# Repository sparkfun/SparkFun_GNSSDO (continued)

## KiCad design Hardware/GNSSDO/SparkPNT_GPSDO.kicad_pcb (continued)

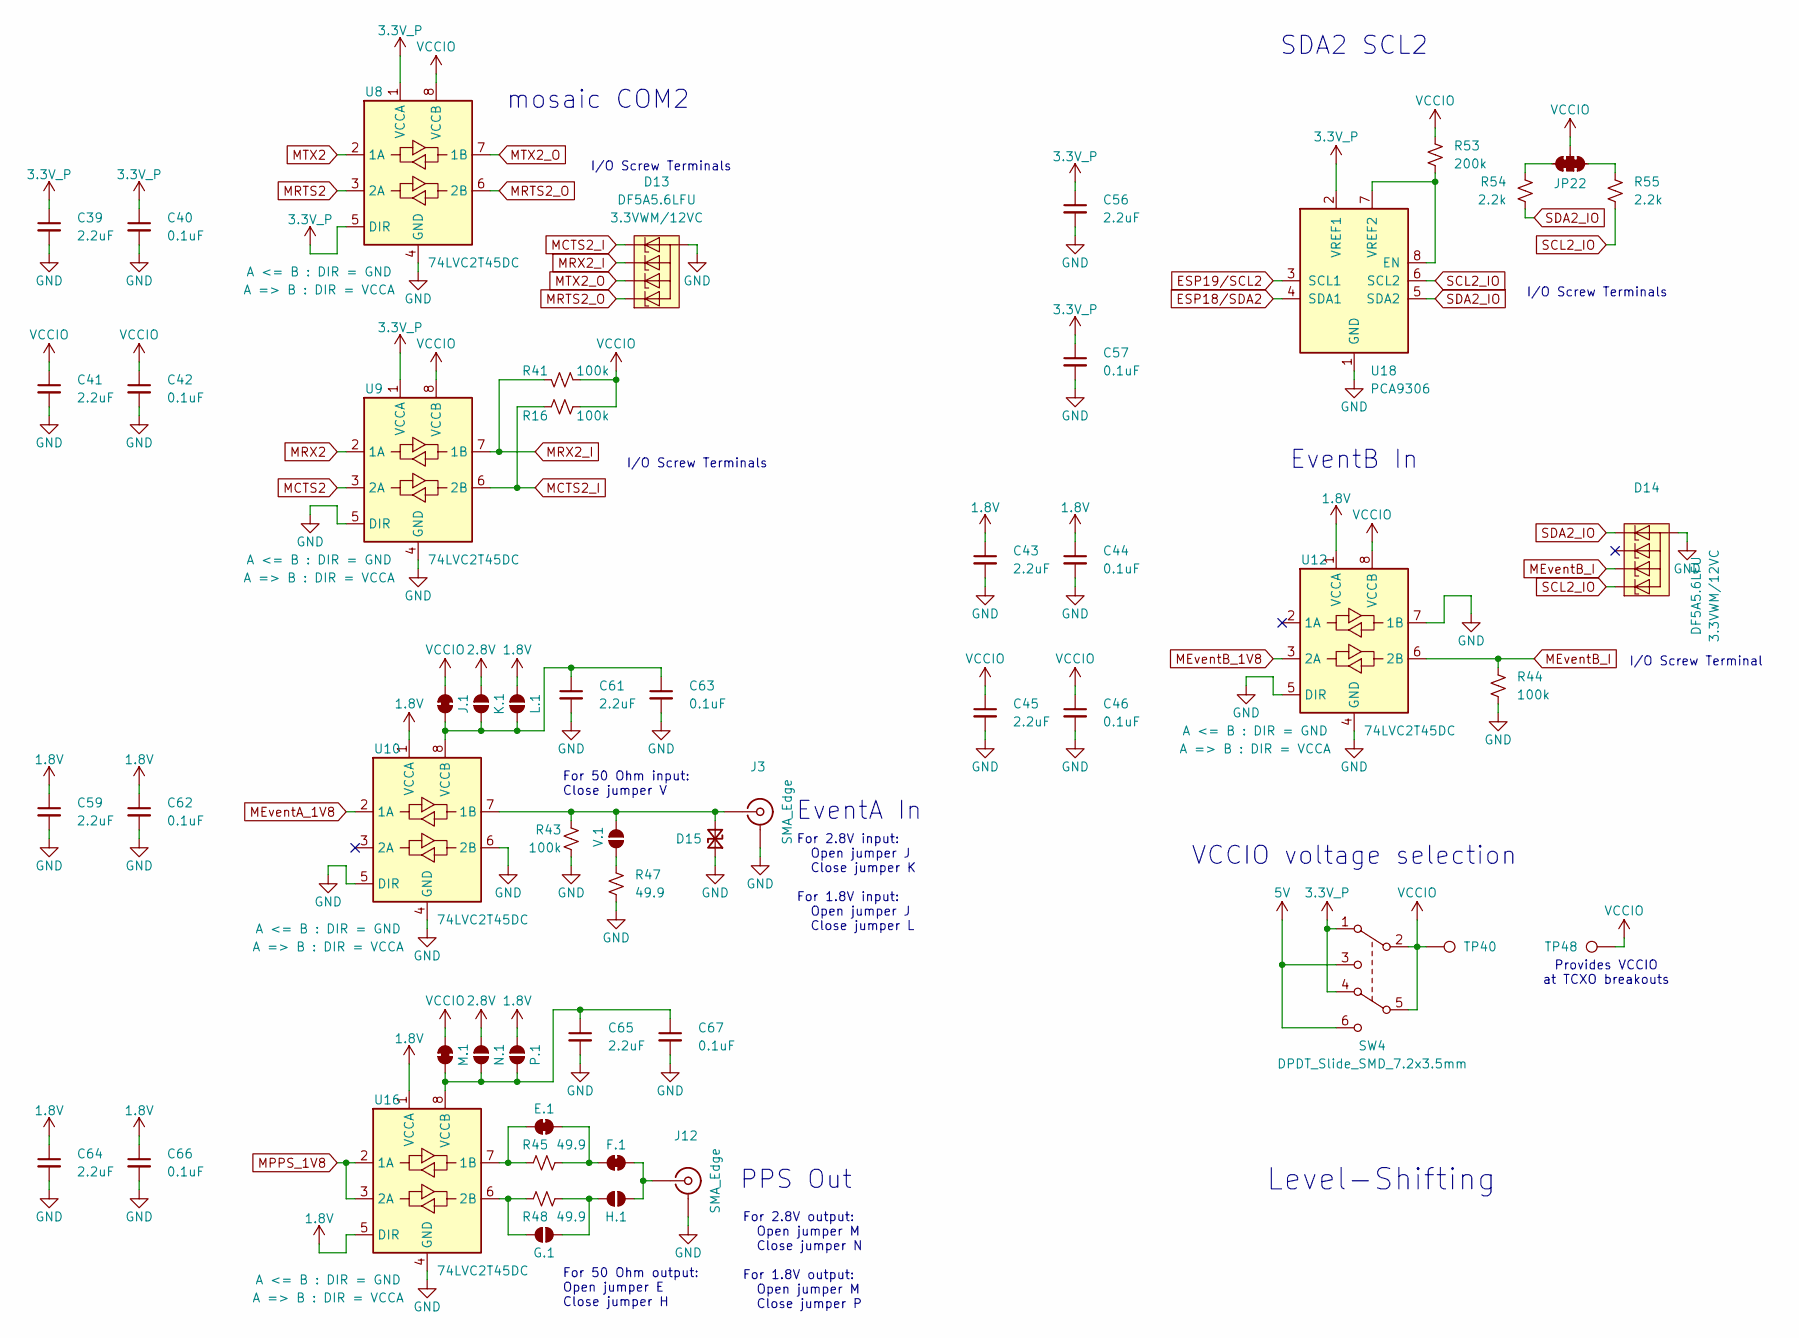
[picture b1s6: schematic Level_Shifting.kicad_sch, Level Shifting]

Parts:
C39, C41, C43, C45, C56, C59, C61, C64, C65: 2.2uF; C_0603_1608Metric; Voltage 10V; Tolerance 20%
C40, C42, C44, C46, C57, C62, C63, C66, C67: 0.1uF; C_0603_1608Metric; Voltage 25V; Tolerance 20%
D13, D14: DF5A5.6LFU; SOT-353; Rating 3.3VWM/12VC
D15: PESD0402; C_0402_1005Metric; Rating 14VWM/40VC
E.1: Jumper_2_NC_Trace
F.1: Jumper_2_NC_Trace
G.1: Jumper_2_NO
H.1: Jumper_2_NO
J3, J12: SMA_Edge; SMA_Edge_6.3mm
J.1: Jumper_2_NC_Trace
JP22: Jumper_3_NC-2_Trace
K.1: Jumper_2_NO
L.1: Jumper_2_NO
M.1: Jumper_2_NC_Trace
N.1: Jumper_2_NO
P.1: Jumper_2_NO
R16, R41, R43, R44: 100k; R_0603_1608Metric
R45, R47, R48: 49.9; R_0603_1608Metric; Tolerance 1%
R53: 200k; R_0603_1608Metric
R54, R55: 2.2k; R_0603_1608Metric
SW4: DPDT_Slide_SMD_7.2x3.5mm; Slide_DPDT_SMD_7.2x3.5mm; Mfg Part# ABC
TP40, TP48: PTH; 1x01_P2.54mm
U8, U9, U10, U12, U16: 74LVC2T45DC; VSSOP8_SOT765-1
U18: PCA9306; VSSOP8_SOT765-1
V.1: Jumper_2_NO

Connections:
1.8V: C43.1, C44.1, C59.1, C62.1, C64.1, C66.1, L.1.2 (B), P.1.2 (B), U10.1 (VCCA), U12.1 (VCCA), U16.1 (VCCA), U16.5 (DIR); also elsewhere on the board
2.8V: K.1.2 (B), N.1.2 (B); also elsewhere on the board
3.3V_P: C39.1, C40.1, C56.1, C57.1, SW4.1 (A), SW4.4 (A), U8.1 (VCCA), U8.5 (DIR), U9.1 (VCCA), U18.2 (VREF1); also elsewhere on the board
5V: SW4.3 (C), SW4.6 (C); also elsewhere on the board
ESP18/SDA2: U18.4 (SDA1); also elsewhere on the board
ESP19/SCL2: U18.3 (SCL1); also elsewhere on the board
GND: C39.2, C40.2, C41.2, C42.2, C43.2, C44.2, C45.2, C46.2, C56.2, C57.2, C59.2, C61.2, C62.2, C63.2, C64.2, C65.2, C66.2, C67.2, D13.2 (A), D14.2 (A), D15.1 (A1), J3.2 (Ext), J12.2 (Ext), R43.1, R44.1, R47.2, U8.4 (GND), U9.4 (GND), U9.5 (DIR), U10.4 (GND), U10.5 (DIR), U10.6 (2B), U12.4 (GND), U12.5 (DIR), U12.7 (1B), U16.4 (GND), U18.1 (GND); also elsewhere on the board
MCTS2: U9.3 (2A); also elsewhere on the board
MCTS2_I: D13.5 (K4), R16.1, U9.6 (2B); also elsewhere on the board
MEventA_1V8: U10.2 (1A); also elsewhere on the board
MEventB_1V8: U12.3 (2A); also elsewhere on the board
MEventB_I: D14.3 (K2), R44.2, U12.6 (2B); also elsewhere on the board
MPPS_1V8: U16.2 (1A), U16.3 (2A); also elsewhere on the board
MRTS2: U8.3 (2A); also elsewhere on the board
MRTS2_O: D13.1 (K1), U8.6 (2B); also elsewhere on the board
MRX2: U9.2 (1A); also elsewhere on the board
MRX2_I: D13.4 (K3), R41.1, U9.7 (1B); also elsewhere on the board
MTX2: U8.2 (1A); also elsewhere on the board
MTX2_O: D13.3 (K2), U8.7 (1B); also elsewhere on the board
unnamed: D15.2 (A2), J3.1 (In), R43.2, U10.7 (1B), V.1.2 (B)
unnamed: E.1.1 (A), R45.1, U16.7 (1B)
unnamed: E.1.2 (B), F.1.1 (A), R45.2
unnamed: F.1.2 (B), H.1.2 (B), J12.1 (In)
unnamed: G.1.1 (A), R48.1, U16.6 (2B)
unnamed: G.1.2 (B), H.1.1 (A), R48.2
unnamed: C61.1, C63.1, J.1.1 (A), K.1.1 (A), L.1.1 (A), U10.8 (VCCB)
unnamed: JP22.1 (A), R55.1
unnamed: JP22.3 (C), R54.1
unnamed: C65.1, C67.1, M.1.1 (A), N.1.1 (A), P.1.1 (A), U16.8 (VCCB)
unnamed: R53.2, U18.7 (VREF2), U18.8 (EN)
unnamed: R47.1, V.1.1 (A)
SCL2_IO: D14.1 (K1), R55.2, U18.6 (SCL2); also elsewhere on the board
SDA2_IO: D14.5 (K4), R54.2, U18.5 (SDA2); also elsewhere on the board
VCCIO: C41.1, C42.1, C45.1, C46.1, J.1.2 (B), JP22.2 (B), M.1.2 (B), R16.2, R41.2, R53.1, SW4.2 (B), SW4.5 (B), TP40.1 (1_1), TP48.1 (1_1), U8.8 (VCCB), U9.8 (VCCB), U12.8 (VCCB); also elsewhere on the board

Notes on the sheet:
SDA2 SCL2
I/O Screw Terminals
Provides VCCIO at TCXO breakouts
For 50 Ohm input: Close jumper V
mosaic COM2
I/O Screw Terminal
Level-Shifting
For 50 Ohm output: Open jumper E Close jumper H
For 2.8V input: Open jumper J Close jumper K For 1.8V input: Open jumper J Close jumper L
For 2.8V output: Open jumper M Close jumper N For 1.8V output: Open jumper M Close jumper P
EventB In
EventA In
PPS Out
VCCIO voltage selection

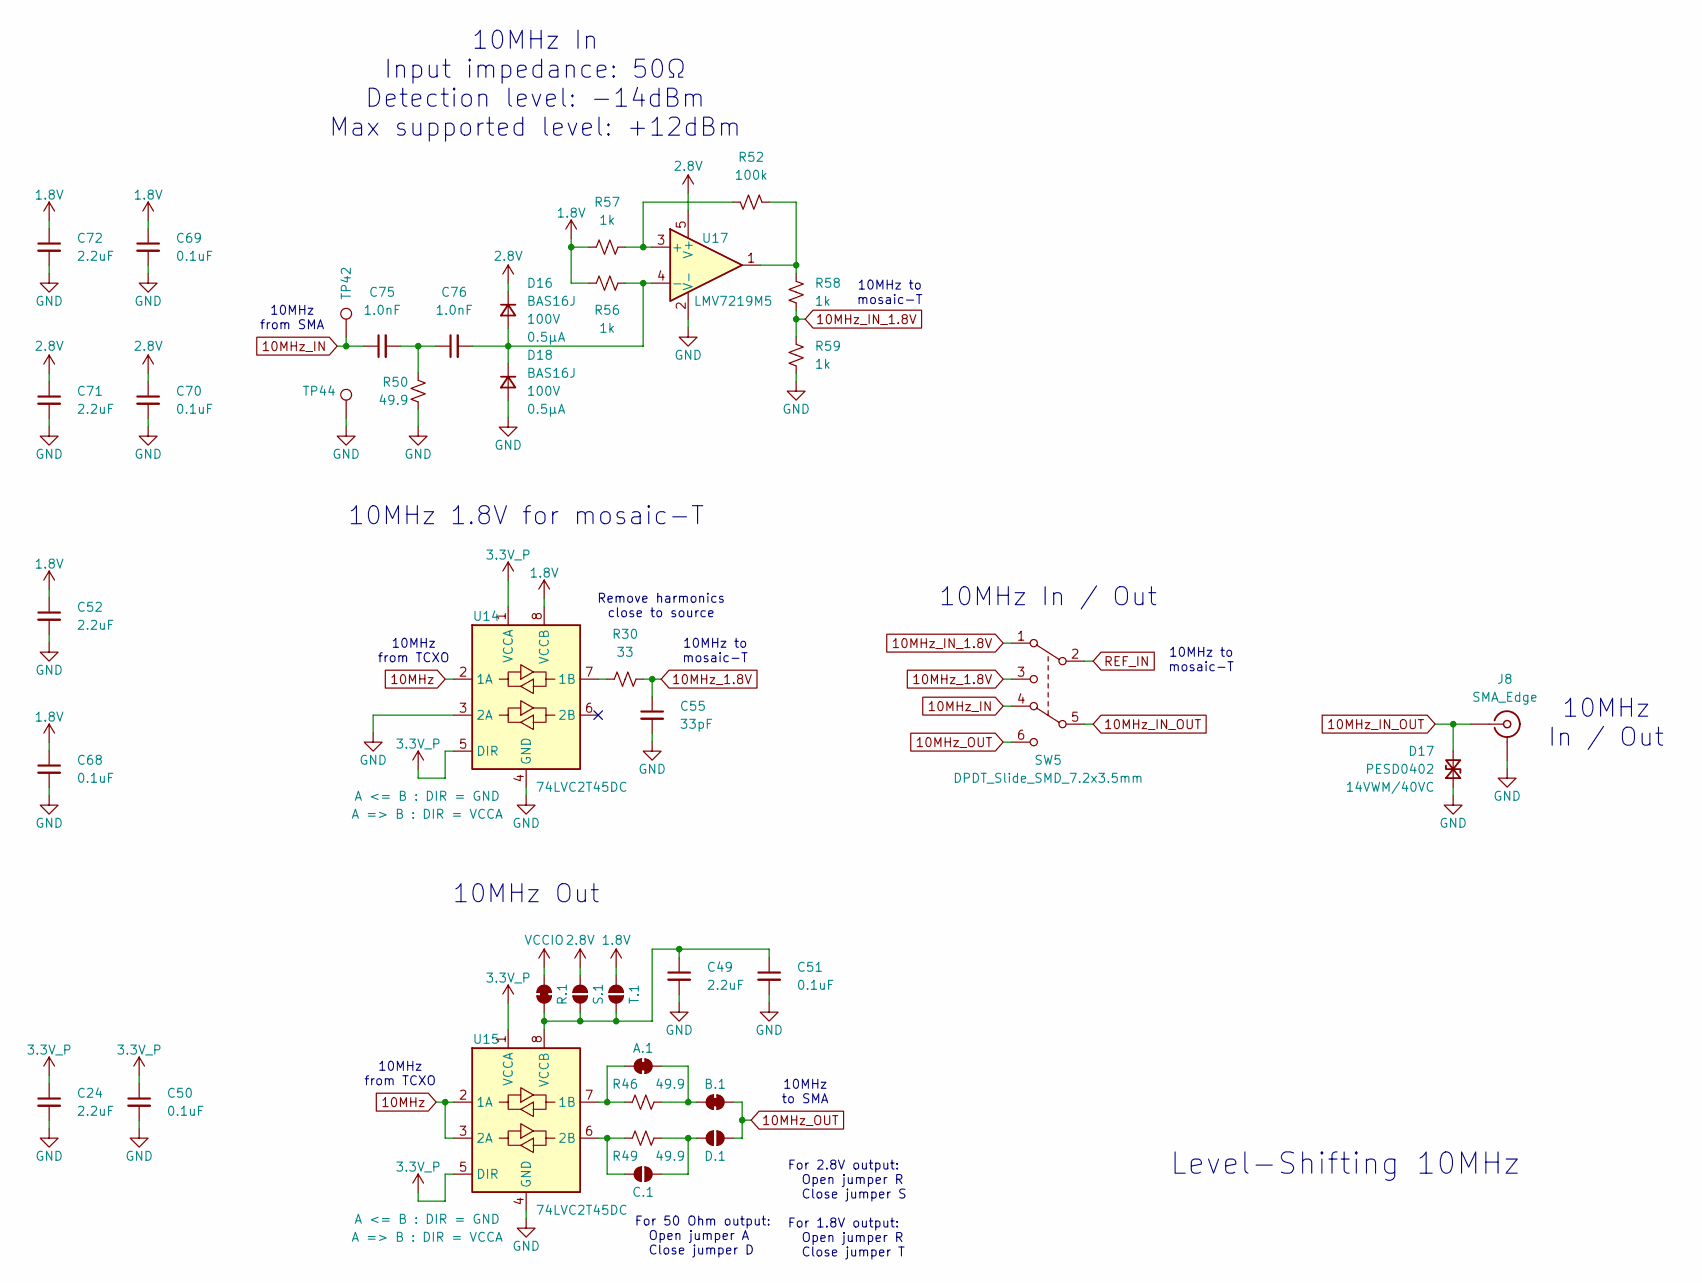
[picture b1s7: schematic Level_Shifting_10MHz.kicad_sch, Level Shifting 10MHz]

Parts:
A.1: Jumper_2_NC_Trace
B.1: Jumper_2_NC_Trace
C24, C49, C52, C71, C72: 2.2uF; C_0603_1608Metric; Voltage 10V; Tolerance 20%
C50, C51, C68, C69, C70: 0.1uF; C_0603_1608Metric; Voltage 25V; Tolerance 20%
C55: 33pF; C_0603_1608Metric; Voltage 50V; Tolerance 5%
C75, C76: 1.0nF; C_0603_1608Metric; Voltage 50V; Tolerance 10%
C.1: Jumper_2_NO
D16, D18: BAS16J; SOD-323
D17: PESD0402; C_0402_1005Metric; Rating 14VWM/40VC
D.1: Jumper_2_NO
J8: SMA_Edge; SMA_Edge_6.3mm
R30: 33; R_0603_1608Metric
R46, R49, R50: 49.9; R_0603_1608Metric; Tolerance 1%
R52: 100k; R_0603_1608Metric
R56, R57, R58, R59: 1k; R_0603_1608Metric
R.1: Jumper_2_NC_Trace
S.1: Jumper_2_NO
SW5: DPDT_Slide_SMD_7.2x3.5mm; Slide_DPDT_SMD_7.2x3.5mm; Mfg Part# ABC
T.1: Jumper_2_NO
TP42, TP44: PTH; 1x01_P2.54mm
U14, U15: 74LVC2T45DC; VSSOP8_SOT765-1
U17: LMV7219M5; SOT23-5

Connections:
1.8V: C52.1, C68.1, C69.1, C72.1, R56.2, R57.2, T.1.2 (B), U14.8 (VCCB); also elsewhere on the board
2.8V: C70.1, C71.1, D16.1 (K), S.1.2 (B), U17.5 (V+); also elsewhere on the board
3.3V_P: C24.1, C50.1, U14.1 (VCCA), U14.5 (DIR), U15.1 (VCCA), U15.5 (DIR); also elsewhere on the board
10MHz: U14.2 (1A), U15.2 (1A), U15.3 (2A); also elsewhere on the board
10MHz_1.8V: C55.1, R30.2, SW5.3 (C)
10MHz_IN: C75.1, SW5.4 (A), TP42.1 (1_1)
10MHz_IN_1.8V: R58.2, R59.1, SW5.1 (A)
10MHz_IN_OUT: D17.2 (A2), J8.1 (In), SW5.5 (B)
10MHz_OUT: B.1.2 (B), D.1.2 (B), SW5.6 (C)
GND: C24.2, C49.2, C50.2, C51.2, C52.2, C55.2, C68.2, C69.2, C70.2, C71.2, C72.2, D17.1 (A1), D18.2 (A), J8.2 (Ext), R50.2, R59.2, TP44.1 (1_1), U14.3 (2A), U14.4 (GND), U15.4 (GND), U17.2 (V-); also elsewhere on the board
unnamed: A.1.1 (A), R46.1, U15.7 (1B)
unnamed: A.1.2 (B), B.1.1 (A), R46.2
unnamed: C75.2, C76.1, R50.1
unnamed: C.1.1 (A), R49.1, U15.6 (2B)
unnamed: C.1.2 (B), D.1.1 (A), R49.2
unnamed: C76.2, D16.2 (A), D18.1 (K), R56.1, U17.4 (-)
unnamed: R52.2, R58.1, U17.1
unnamed: C49.1, C51.1, R.1.1 (A), S.1.1 (A), T.1.1 (A), U15.8 (VCCB)
unnamed: R30.1, U14.7 (1B)
unnamed: R52.1, R57.1, U17.3 (+)
REF_IN: SW5.2 (B); also elsewhere on the board
VCCIO: R.1.2 (B); also elsewhere on the board

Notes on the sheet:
10MHz from TCXO
10MHz from SMA
10MHz to mosaic-T
10MHz In Input impedance: 50Ω Detection level: -14dBm Max supported level: +12dBm
For 50 Ohm output: Open jumper A Close jumper D
10MHz In / Out
Remove harmonics close to source
For 2.8V output: Open jumper R Close jumper S For 1.8V output: Open jumper R Close jumper T
10MHz 1.8V for mosaic-T
Level-Shifting 10MHz
10MHz to SMA
10MHz In / Out
10MHz Out

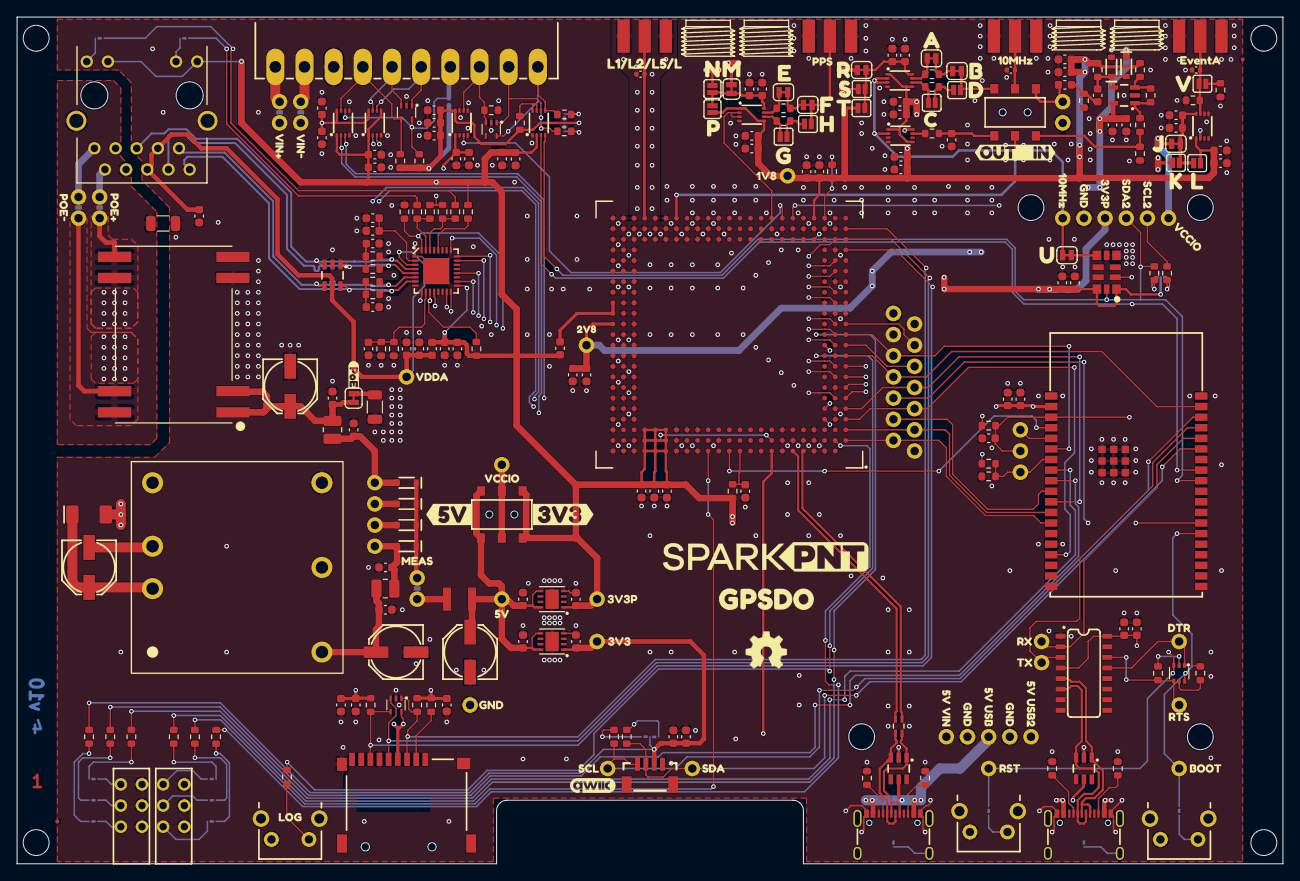
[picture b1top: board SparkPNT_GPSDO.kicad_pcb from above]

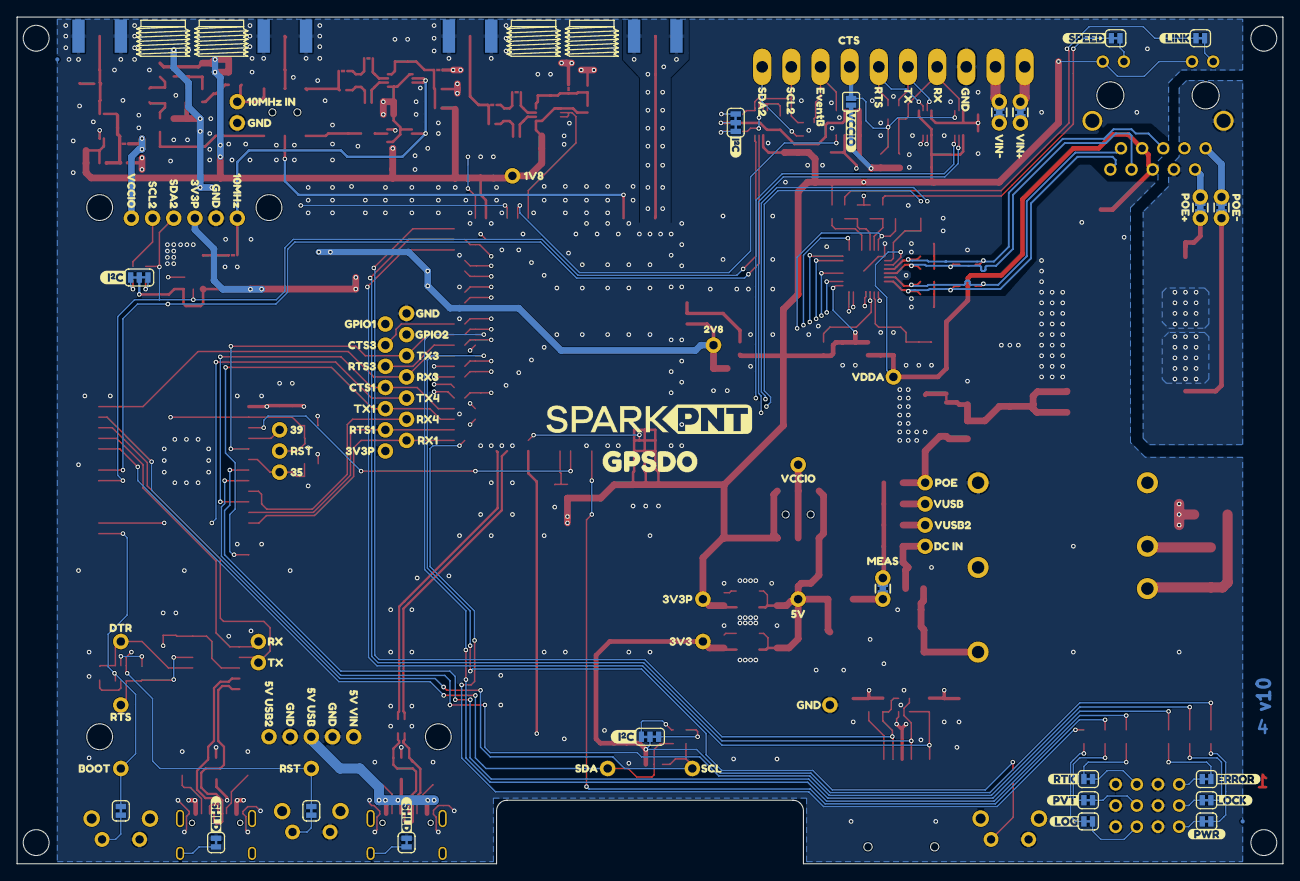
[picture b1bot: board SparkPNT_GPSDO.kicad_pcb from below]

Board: 4 copper layers, 151.9 x 101.6 mm, 435 parts (101 on the bottom side), 169 nets.

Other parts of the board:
Ref**: Val**; OSHW_Logo_5mm
kibuzzard-65A7F5A7: G***; kibuzzard-65A7F5A7
kibuzzard-65A7F5BC: G***; kibuzzard-65A7F5BC
kibuzzard-65A7F5CF: G***; kibuzzard-65A7F5CF
kibuzzard-65A7F5E3: G***; kibuzzard-65A7F5E3
kibuzzard-65A7F440, kibuzzard-65A7F440#2: G***; kibuzzard-65A7F440
kibuzzard-65A7F499: G***; kibuzzard-65A7F499
kibuzzard-65A7F511, kibuzzard-65A7F511#2: G***; kibuzzard-65A7F511
kibuzzard-65A7F548, kibuzzard-65A7F548#2: G***; kibuzzard-65A7F548
kibuzzard-65A7F771, kibuzzard-65A7F771#2: G***; kibuzzard-65A7F771
kibuzzard-65A7F891, kibuzzard-65A7F891#2: G***; kibuzzard-65A7F891
kibuzzard-66A11DB0: G***; kibuzzard-66A11DB0
kibuzzard-66A11DCF: G***; kibuzzard-66A11DCF
kibuzzard-66A11DE1: G***; kibuzzard-66A11DE1
kibuzzard-66A11DF6: G***; kibuzzard-66A11DF6
kibuzzard-66A11E3D: G***; kibuzzard-66A11E3D
kibuzzard-66A11E07: G***; kibuzzard-66A11E07
kibuzzard-66A11E7B: G***; kibuzzard-66A11E7B
kibuzzard-66A11E14: G***; kibuzzard-66A11E14
kibuzzard-66A11E22: G***; kibuzzard-66A11E22
kibuzzard-66A11E31: G***; kibuzzard-66A11E31
kibuzzard-66A11E48: G***; kibuzzard-66A11E48
kibuzzard-66A11E61: G***; kibuzzard-66A11E61
kibuzzard-66A11EB6, kibuzzard-66A11EB6#2: G***; kibuzzard-66A11EB6
kibuzzard-66A11ECA, kibuzzard-66A11ECA#2: G***; kibuzzard-66A11ECA
kibuzzard-66A11ED7, kibuzzard-66A11ED7#2, kibuzzard-66A11ED7#3: G***; kibuzzard-66A11ED7
kibuzzard-66A11EE6, kibuzzard-66A11EE6#2: G***; kibuzzard-66A11EE6
kibuzzard-66A11EF1, kibuzzard-66A11EF1#2: G***; kibuzzard-66A11EF1
kibuzzard-66A11F9C: G***; kibuzzard-66A11F9C
kibuzzard-66A11F21, kibuzzard-66A11F21#2: G***; kibuzzard-66A11F21
kibuzzard-66A11F39, kibuzzard-66A11F39#2: G***; kibuzzard-66A11F39
kibuzzard-66A11FB3: G***; kibuzzard-66A11FB3
kibuzzard-66A11FEE, kibuzzard-66A11FEE#2: G***; kibuzzard-66A11FEE
kibuzzard-66A36AE8, kibuzzard-66A36AE8#2: G***; kibuzzard-66A36AE8
kibuzzard-66A36B1F: G***; kibuzzard-66A36B1F
kibuzzard-66A36BEE: G***; kibuzzard-66A36BEE
kibuzzard-66A120AA: G***; kibuzzard-66A120AA
kibuzzard-66A120EB: G***; kibuzzard-66A120EB
kibuzzard-66A121BE, kibuzzard-66A121BE#2: G***; kibuzzard-66A121BE
kibuzzard-66A121D2, kibuzzard-66A121D2#2: G***; kibuzzard-66A121D2
kibuzzard-66A122A4, kibuzzard-66A122A4#2: G***; kibuzzard-66A122A4
kibuzzard-66A122D2, kibuzzard-66A122D2#2: G***; kibuzzard-66A122D2
kibuzzard-66A211A5: G***; kibuzzard-66A211A5
kibuzzard-66A212C6: G***; kibuzzard-66A212C6
kibuzzard-66A212DB: G***; kibuzzard-66A212DB
kibuzzard-66A212E8: G***; kibuzzard-66A212E8
kibuzzard-66A212F8: G***; kibuzzard-66A212F8
kibuzzard-66A1201E: G***; kibuzzard-66A1201E
kibuzzard-66A1223B, kibuzzard-66A1223B#2: G***; kibuzzard-66A1223B
kibuzzard-66A2129F: G***; kibuzzard-66A2129F
kibuzzard-66A12010: G***; kibuzzard-66A12010
kibuzzard-66A12027: G***; kibuzzard-66A12027
kibuzzard-66A12034: G***; kibuzzard-66A12034
kibuzzard-66A12099: G***; kibuzzard-66A12099
kibuzzard-66A12140: G***; kibuzzard-66A12140
kibuzzard-66A12152: G***; kibuzzard-66A12152
kibuzzard-66A12161: G***; kibuzzard-66A12161
kibuzzard-66A12184, kibuzzard-66A12184#2: G***; kibuzzard-66A12184
kibuzzard-66A12197, kibuzzard-66A12197#2: G***; kibuzzard-66A12197
kibuzzard-66A12248, kibuzzard-66A12248#2: G***; kibuzzard-66A12248
kibuzzard-66A12259, kibuzzard-66A12259#2: G***; kibuzzard-66A12259
kibuzzard-66A12273, kibuzzard-66A12273#2: G***; kibuzzard-66A12273
kibuzzard-66A12315, kibuzzard-66A12315#2: G***; kibuzzard-66A12315
kibuzzard-66A12334, kibuzzard-66A12334#2: G***; kibuzzard-66A12334
kibuzzard-66A12372, kibuzzard-66A12372#2: G***; kibuzzard-66A12372
kibuzzard-66A21191: G***; kibuzzard-66A21191
kibuzzard-66A21255: G***; kibuzzard-66A21255
kibuzzard-66A21310: G***; kibuzzard-66A21310
kibuzzard-66A21341: G***; kibuzzard-66A21341
kibuzzard-66A21351: G***; kibuzzard-66A21351
kibuzzard-672DF8D1, kibuzzard-672DF8D1#2: G***; kibuzzard-672DF8D1
kibuzzard-672DF8E6, kibuzzard-672DF8E6#2, kibuzzard-672DF8E6#3, kibuzzard-672DF8E6#4: G***; kibuzzard-672DF8E6
kibuzzard-672DF612, kibuzzard-672DF612#2: G***; kibuzzard-672DF612
kibuzzard-672DF903, kibuzzard-672DF903#2: G***; kibuzzard-672DF903
kibuzzard-6710F8E6: G***; kibuzzard-6710F8E6
kibuzzard-6717B47E: G***; kibuzzard-6717B47E
kibuzzard-6717B190: G***; kibuzzard-6717B190
kibuzzard-6718A8DE, kibuzzard-6718A8DE#2: G***; kibuzzard-6718A8DE
kibuzzard-6718A746: G***; kibuzzard-6718A746
kibuzzard-6718C618: G***; kibuzzard-6718C618
kibuzzard-65776CDC: G***; kibuzzard-65776CDC
kibuzzard-67126CA7: G***; kibuzzard-67126CA7
kibuzzard-67127BF9, kibuzzard-67127BF9#2: G***; kibuzzard-67127BF9
kibuzzard-67162BBE: G***; kibuzzard-67162BBE
kibuzzard-67162BCC: G***; kibuzzard-67162BCC
kibuzzard-67162BE4: G***; kibuzzard-67162BE4
kibuzzard-67163F4F: G***; kibuzzard-67163F4F
kibuzzard-67163F31: G***; kibuzzard-67163F31
kibuzzard-67163F40: G***; kibuzzard-67163F40
kibuzzard-671267A7: G***; kibuzzard-671267A7
kibuzzard-671267CF: G***; kibuzzard-671267CF
kibuzzard-671267DB: G***; kibuzzard-671267DB
kibuzzard-671267FD: G***; kibuzzard-671267FD
kibuzzard-671645B9: G***; kibuzzard-671645B9
kibuzzard-671645D5: G***; kibuzzard-671645D5
kibuzzard-671646EE: G***; kibuzzard-671646EE
kibuzzard-6712235F: G***; kibuzzard-6712235F
kibuzzard-6712236B: G***; kibuzzard-6712236B
kibuzzard-6712680B: G***; kibuzzard-6712680B
kibuzzard-67126756: G***; kibuzzard-67126756
kibuzzard-67126766: G***; kibuzzard-67126766
kibuzzard-67126777: G***; kibuzzard-67126777
kibuzzard-67126820: G***; kibuzzard-67126820
kibuzzard-67126865: G***; kibuzzard-67126865

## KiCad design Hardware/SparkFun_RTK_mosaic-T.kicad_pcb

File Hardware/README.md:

SparkFun GPSDO Design Files
=====================================

The files here are the KiCad schematic and PCB design files from SparkFun Electronics.

KiCad can be downloaded [here](https://www.kicad.org/).

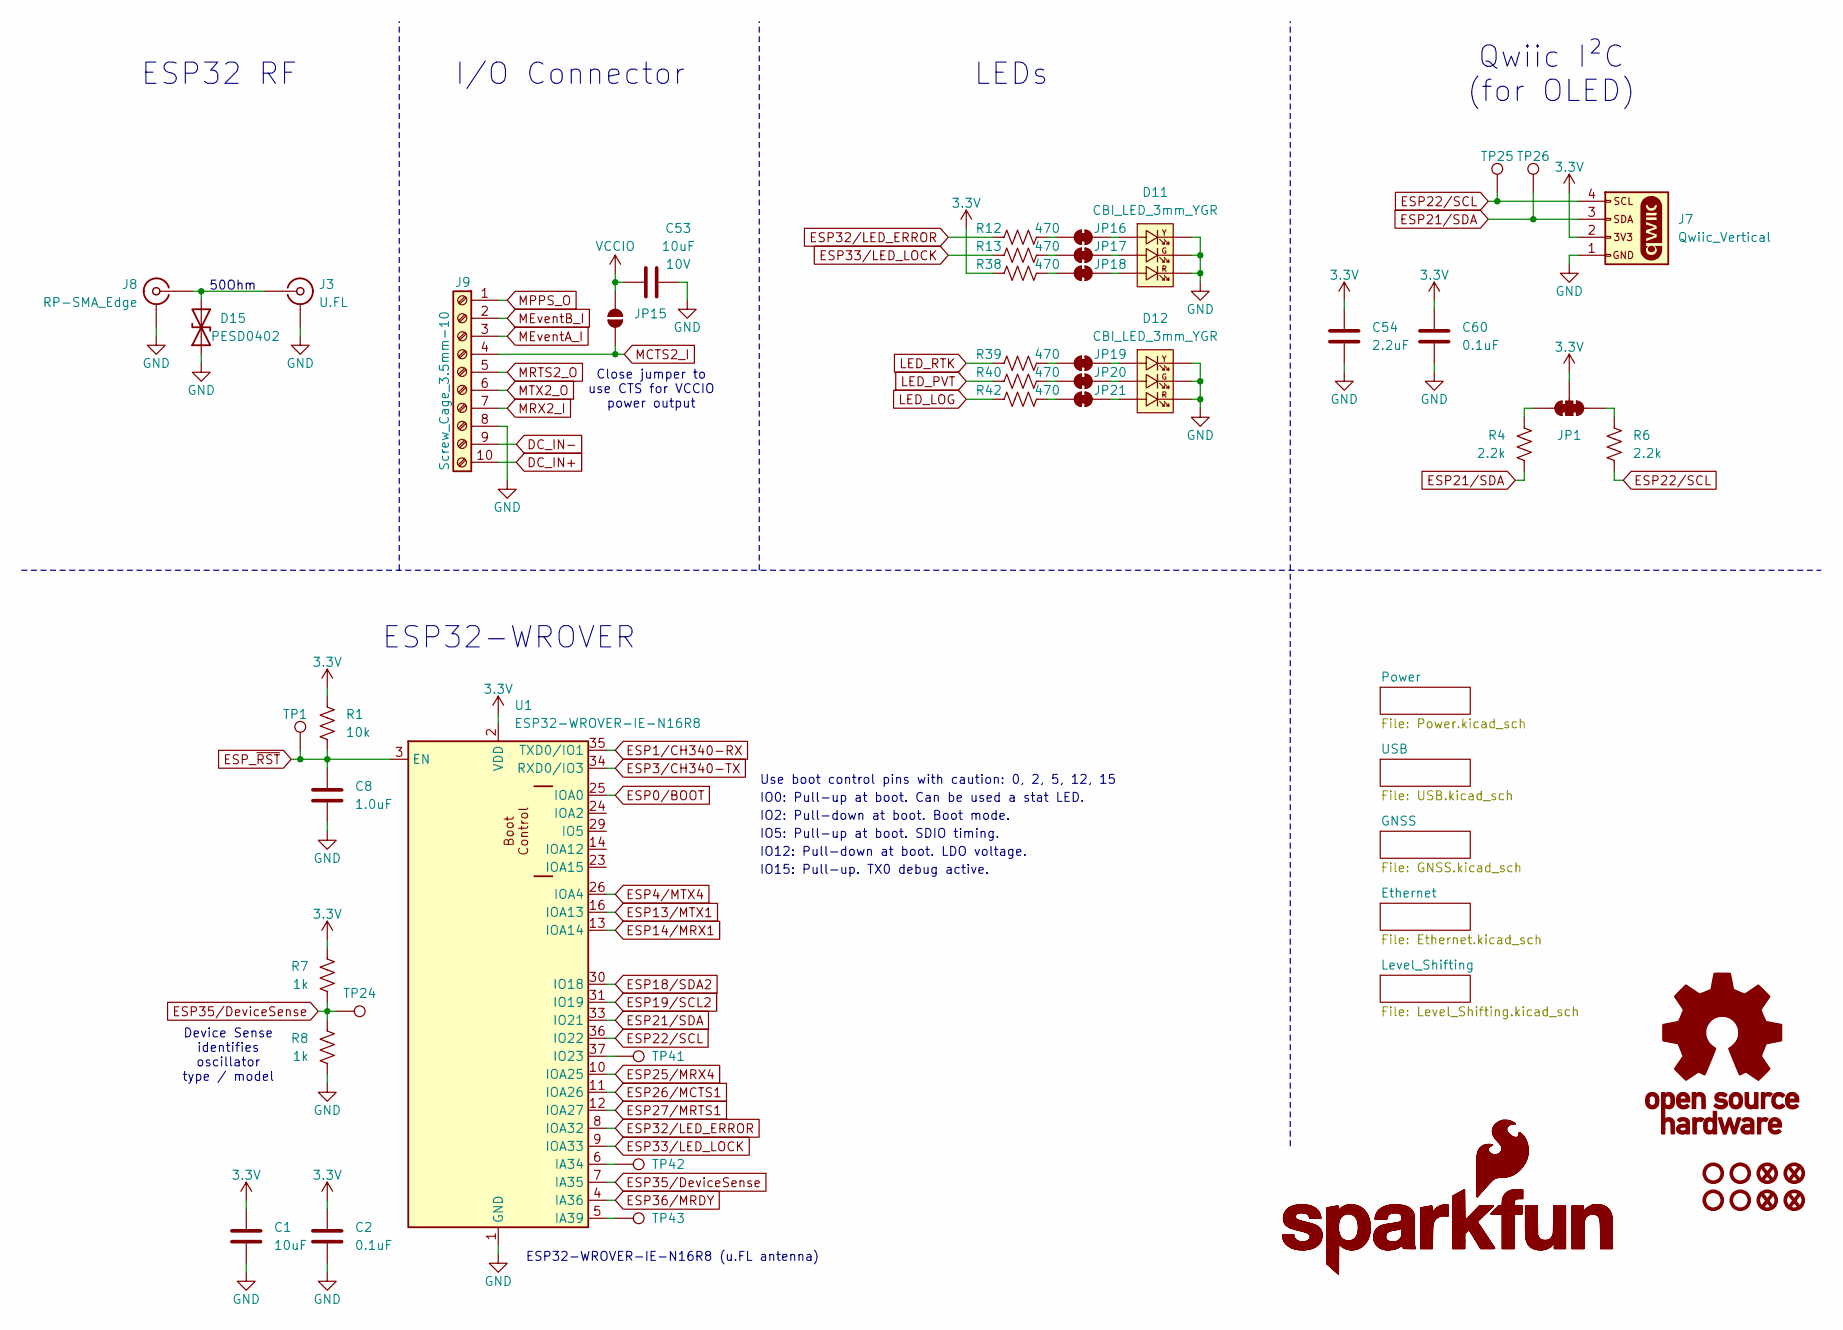
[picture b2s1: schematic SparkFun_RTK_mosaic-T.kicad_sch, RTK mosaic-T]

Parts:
C1: 10uF; C_0603_1608Metric; Voltage 6.3V; Tolerance 20%
C2, C60: 0.1uF; C_0603_1608Metric; Voltage 25V; Tolerance 20%
C8: 1.0uF; C_0603_1608Metric; Voltage 16V; Tolerance 10%
C53: 10uF; C_0603_1608Metric; Voltage 10V; Tolerance 20%
C54: 2.2uF; C_0603_1608Metric; Voltage 10V; Tolerance 20%
D11, D12: CBI_LED_3mm_YGR; CBI_LED_Triple_3mm_PTH
D15: PESD0402; C_0402_1005Metric
FID1, FID2, FID3, FID4: Fiducial_0.5mm; Fiducial_0.5mm_Mask1mm
G1: OSHW_Logo; Creative_Commons_License
G3, G5: SparkFun_Logo
J3: U.FL
J7: Qwiic_Vertical; JST_SMD_1.0mm-4_Vertical
J8: RP-SMA_Edge
J9: Screw_Cage_3.5mm-10
JP1: Jumper_3_NC-2_Trace
JP15: Jumper_2_NO
JP16, JP17, JP18, JP19, JP20, JP21: Jumper_2_NC_Trace
R1: 10k; R_0603_1608Metric
R4, R6: 2.2k; R_0603_1608Metric
R7, R8: 1k; R_0603_1608Metric
R12, R13, R38, R39, R40, R42: 470; R_0603_1608Metric
ST1, ST2, ST3, ST4: Standoff
TP1, TP24, TP25, TP26, TP41, TP42, TP43: PTH; 1x01
U1: ESP32-WROVER-IE-N16R8; ESP32-WROVER-E-IE

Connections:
3.3V: C1.1, C2.1, C54.1, C60.1, J7.2, JP1.2 (C), R1.1, R7.1, R38.2, U1.2 (VDD); also elsewhere on the board
DC_IN+: J9.10 (Pin_1); also elsewhere on the board
DC_IN-: J9.9 (Pin_1); also elsewhere on the board
ESP0/BOOT: U1.25 (IOA0); also elsewhere on the board
ESP1/CH340-RX: U1.35 (TXD0/IO1); also elsewhere on the board
ESP3/CH340-TX: U1.34 (RXD0/IO3); also elsewhere on the board
ESP4/MTX4: U1.26 (IOA4); also elsewhere on the board
ESP13/MTX1: U1.16 (IOA13); also elsewhere on the board
ESP14/MRX1: U1.13 (IOA14); also elsewhere on the board
ESP18/SDA2: U1.30 (IO18); also elsewhere on the board
ESP19/SCL2: U1.31 (IO19); also elsewhere on the board
ESP21/SDA: J7.3, R4.1, TP26.1, U1.33 (IO21)
ESP22/SCL: J7.4, R6.1, TP25.1, U1.36 (IO22)
ESP25/MRX4: U1.10 (IOA25); also elsewhere on the board
ESP26/MCTS1: U1.11 (IOA26); also elsewhere on the board
ESP27/MRTS1: U1.12 (IOA27); also elsewhere on the board
ESP32/LED_ERROR: R12.2, U1.8 (IOA32)
ESP33/LED_LOCK: R13.2, U1.9 (IOA33)
ESP35/DeviceSense: R7.2, R8.1, TP24.1, U1.7 (IA35)
ESP36/MRDY: U1.4 (IA36); also elsewhere on the board
ESP_~RST: C8.1, R1.2, TP1.1, U1.3 (EN); also elsewhere on the board
GND: C1.2, C2.2, C8.2, C53.2, C54.2, C60.2, D11.CATHODE_1, D11.CATHODE_2, D11.CATHODE_3, D12.CATHODE_1, D12.CATHODE_2, D12.CATHODE_3, D15.1 (A1), J3.2 (Ext), J7.1, J8.2 (Ext), J9.8 (Pin_1), R8.2, U1.1 (GND), U1.15 (GND), U1.38 (GND), U1.39.1 (GND), U1.39.2 (GND), U1.39.3 (GND), U1.39.4 (GND), U1.39.5 (GND), U1.39.6 (GND), U1.39.7 (GND), U1.39.8 (GND), U1.39.9 (GND); also elsewhere on the board
LED_LOG: R42.2; also elsewhere on the board
LED_PVT: R40.2; also elsewhere on the board
LED_RTK: R39.2; also elsewhere on the board
MCTS2_I: J9.4, JP15.1 (A); also elsewhere on the board
MEventA_I: J9.3; also elsewhere on the board
MEventB_I: J9.2; also elsewhere on the board
MPPS_O: J9.1; also elsewhere on the board
MRTS2_O: J9.5 (Pin_3); also elsewhere on the board
MRX2_I: J9.7 (Pin_2); also elsewhere on the board
MTX2_O: J9.6 (Pin_4); also elsewhere on the board
unnamed: D15.2 (A2), J3.1 (In), J8.1 (In)
unnamed: JP1.1 (A), R6.2
unnamed: JP1.3 (B), R4.2
unnamed: JP16.1 (A), R12.1
unnamed: D11.ANODE_1, JP16.2 (B)
unnamed: JP17.1 (A), R13.1
unnamed: D11.ANODE_2, JP17.2 (B)
unnamed: JP18.1 (A), R38.1
unnamed: D11.ANODE_3, JP18.2 (B)
unnamed: JP19.1 (A), R39.1
unnamed: D12.ANODE_1, JP19.2 (B)
unnamed: JP20.1 (A), R40.1
unnamed: D12.ANODE_2, JP20.2 (B)
unnamed: JP21.1 (A), R42.1
unnamed: D12.ANODE_3, JP21.2 (B)
unnamed: TP42.1, U1.6 (IA34)
unnamed: TP43.1, U1.5 (IA39)
unnamed: TP41.1, U1.37 (IO23)
VCCIO: C53.1, JP15.2 (B); also elsewhere on the board

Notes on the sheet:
IO15: Pull-up. TX0 debug active.
IO2: Pull-down at boot. Boot mode.
ESP32-WROVER
IO0: Pull-up at boot. Can be used a stat LED.
LEDs
Qwiic I²C (for OLED)
Device Sense identifies oscillator type / model
Close jumper to use CTS for VCCIO power output
IO5: Pull-up at boot. SDIO timing.
ESP32 RF
I/O Connector
Use boot control pins with caution: 0, 2, 5, 12, 15
ESP32-WROVER-IE-N16R8 (u.FL antenna)
IO12: Pull-down at boot. LDO voltage.
50Ohm

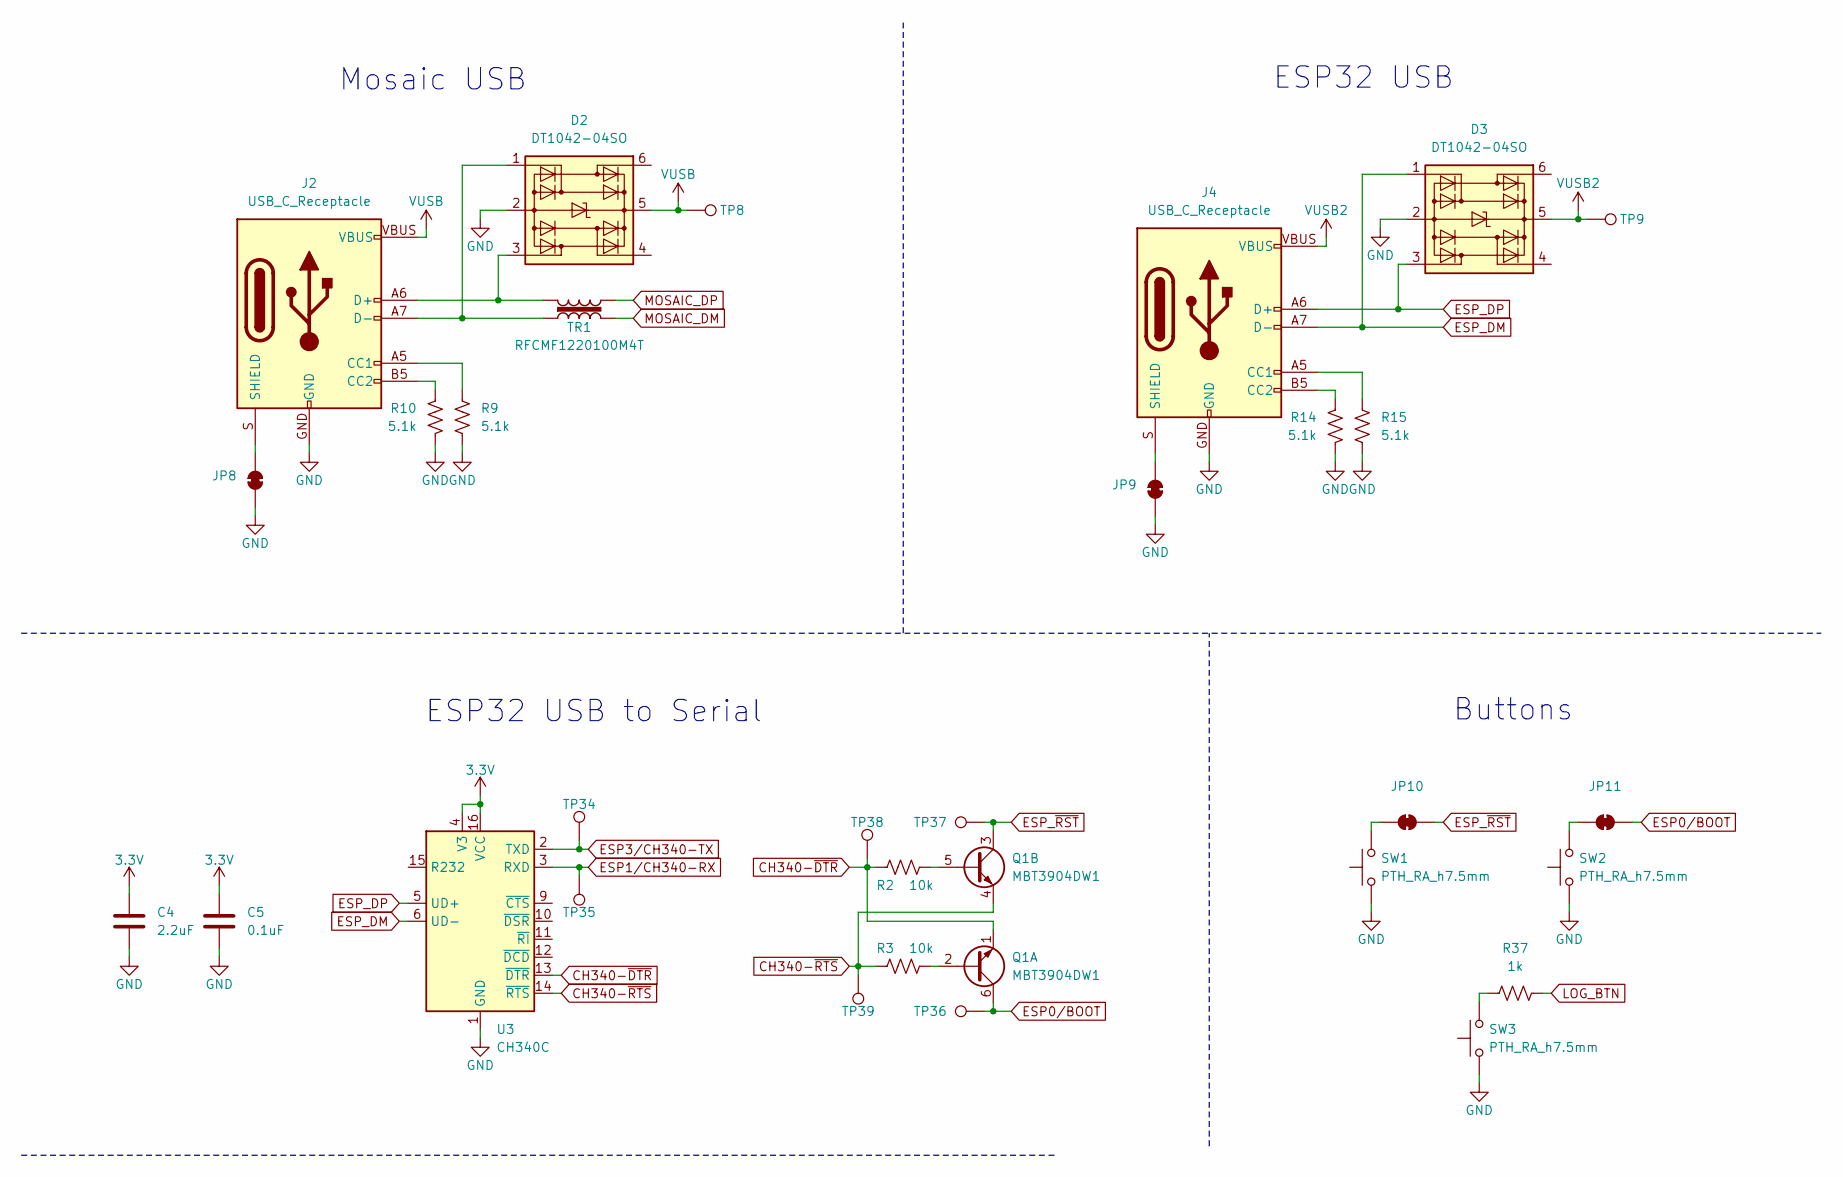
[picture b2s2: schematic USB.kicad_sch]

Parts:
C4: 2.2uF; C_0603_1608Metric; Voltage 10V; Tolerance 20%
C5: 0.1uF; C_0603_1608Metric; Voltage 25V; Tolerance 20%
D2, D3: DT1042-04SO; SOT23-6
J2, J4: USB_C_Receptacle; USB-C_16
JP8, JP9, JP10, JP11: Jumper_2_NC_Trace
Q1: MBT3904DW1; SOT-323
R2, R3: 10k; R_0603_1608Metric
R9, R10, R14, R15: 5.1k; R_0603_1608Metric
R37: 1k; R_0603_1608Metric
SW1, SW2, SW3: PTH_RA_h7.5mm; Push_PTH_RA_8-020_h7.5mm; Mfg Part# 8-020 TS H = 7.5mm
TP8, TP9, TP34, TP35, TP36, TP37, TP38, TP39: PTH; 1x01
TR1: RFCMF1220100M4T
U3: CH340C; SO-16

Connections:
3.3V: C4.1, C5.1, U3.4 (V3), U3.16 (VCC); also elsewhere on the board
CH340-~DTR: Q1.1 (E1), R2.2, TP38.1, U3.13 (~DTR)
CH340-~RTS: Q1.4 (E2), R3.2, TP39.1, U3.14 (~RTS)
ESP0/BOOT: JP11.2 (B), Q1.6 (C1), TP36.1; also elsewhere on the board
ESP1/CH340-RX: TP35.1, U3.3 (RXD); also elsewhere on the board
ESP3/CH340-TX: TP34.1, U3.2 (TXD); also elsewhere on the board
ESP_DM: D3.1 (I/O1), J4.A7 (D-), J4.B7 (D-), U3.6 (UD-)
ESP_DP: D3.3 (I/O2), J4.A6 (D+), J4.B6 (D+), U3.5 (UD+)
ESP_~RST: JP10.2 (B), Q1.3 (C2), TP37.1; also elsewhere on the board
GND: C4.2, C5.2, D2.2 (GND), D3.2 (GND), J2.GND, J4.GND, JP8.1 (A), JP9.1 (A), R9.1, R10.1, R14.1, R15.1, SW1.1, SW2.1, SW3.1, U3.1 (GND); also elsewhere on the board
LOG_BTN: R37.1; also elsewhere on the board
MOSAIC_DM: TR1.4; also elsewhere on the board
MOSAIC_DP: TR1.2; also elsewhere on the board
unnamed: D2.1 (I/O1), J2.A7 (D-), J2.B7 (D-), TR1.3
unnamed: D2.3 (I/O2), J2.A6 (D+), J2.B6 (D+), TR1.1
unnamed: J2.A5 (CC1), R9.2
unnamed: J2.B5 (CC2), R10.2
unnamed: J2.S (SHIELD), JP8.2 (B)
unnamed: J4.A5 (CC1), R15.2
unnamed: J4.B5 (CC2), R14.2
unnamed: J4.S (SHIELD), JP9.2 (B)
unnamed: JP10.1 (A), SW1.2
unnamed: JP11.1 (A), SW2.2
unnamed: Q1.2 (B1), R3.1
unnamed: Q1.5 (B2), R2.1
unnamed: R37.2, SW3.2
VUSB: D2.5 (VCC), J2.VBUS, TP8.1; also elsewhere on the board
VUSB2: D3.5 (VCC), J4.VBUS, TP9.1; also elsewhere on the board

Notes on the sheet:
ESP32 USB to Serial
Mosaic USB
Buttons
ESP32 USB
